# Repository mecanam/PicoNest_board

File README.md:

# PicoNest
ラズパイピコ用の拡張基板です。  
NestBlocksを使用してMicroPythonプログラミングを行います。

## NestBlocks
Scratchのようにブロックでマイコンプログラミング可能な総合開発環境です。  
ブロックは内部でMicroPythonに変換され、マイコンに書き込まれます。
https://nestblocks.jp

# 仕様
- 電源電圧 : 6.5~12V
- サーボ : 4個
- DCモータ : 4個
- ADC : 3個
- GPIO : 5個
- I2C : 2個
- UART : 1個

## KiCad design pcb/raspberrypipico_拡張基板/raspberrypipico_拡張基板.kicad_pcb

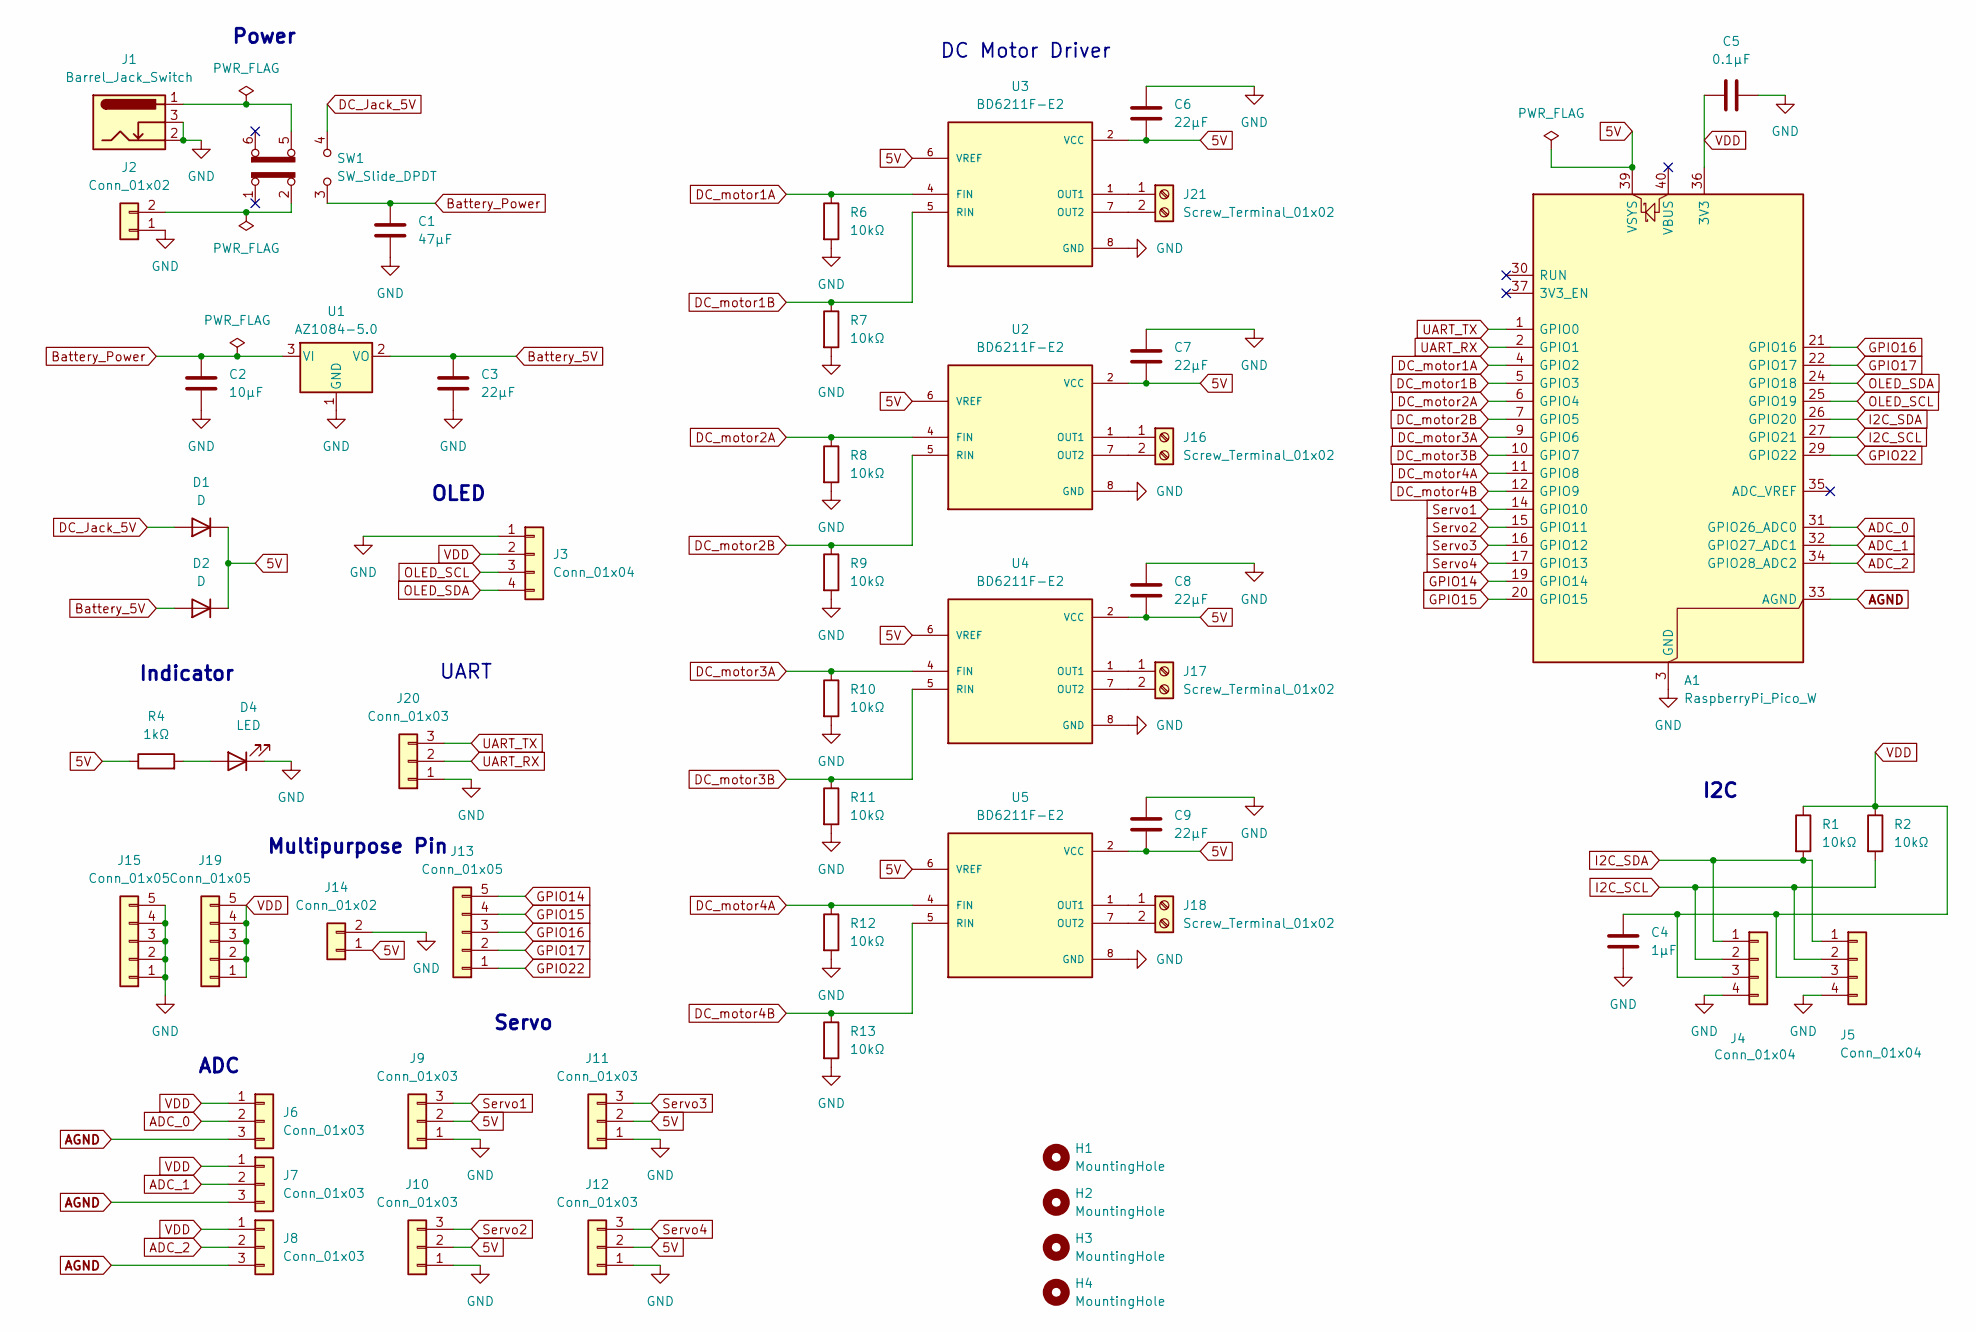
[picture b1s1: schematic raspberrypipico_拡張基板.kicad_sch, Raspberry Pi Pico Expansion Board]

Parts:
A1: RaspberryPi_Pico_W; RaspberryPi_Pico_Common_THT
C1: 47μF; C_Elec_6.3x7.7
C2: 10μF; C_0603_1608Metric_Pad1.08x0.95mm_HandSolder
C3: 22μF; C_0603_1608Metric_Pad1.08x0.95mm_HandSolder
C4: 1μF; C_0603_1608Metric_Pad1.08x0.95mm_HandSolder
C5: 0.1μF; C_0603_1608Metric_Pad1.08x0.95mm_HandSolder
C6, C7, C8, C9: 22μF; C_Elec_6.3x7.7
D1, D2: D; D_SMB_Handsoldering
D4: LED; LED_0603_1608Metric_Pad1.05x0.95mm_HandSolder
H1, H2, H3, H4: MountingHole; MountingHole_3.2mm_M3
J1: Barrel_Jack_Switch; BarrelJack_Horizontal
J2: Conn_01x02; JST_XH_S2B-XH-A_1x02_P2.50mm_Horizontal
J3: Conn_01x04; PinHeader_1x04_P2.54mm_Vertical
J4, J5: Conn_01x04; JST_XH_B4B-XH-A_1x04_P2.50mm_Vertical
J6, J7, J8, J9, J10, J11, J12, J20: Conn_01x03; PinHeader_1x03_P2.54mm_Vertical
J13, J15, J19: Conn_01x05; PinHeader_1x05_P2.54mm_Vertical
J14: Conn_01x02; PinHeader_1x02_P2.54mm_Vertical
J16, J17, J18, J21: Screw_Terminal_01x02; TerminalBlock_bornier-2_P5.08mm
R1, R2, R6, R7, R8, R9, R10, R11, R12, R13: 10kΩ; R_0603_1608Metric_Pad0.98x0.95mm_HandSolder
R4: 1kΩ; R_0603_1608Metric_Pad0.98x0.95mm_HandSolder
SW1: SW_Slide_DPDT; SS22F06G5-G
U1: AZ1084-5.0; TO-252-2
U2, U3, U4, U5: BD6211F-E2; SSOP-8_3.95x5.21x3.27mm_P1.27mm; PARTREV 003

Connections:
5V: A1.39 (VSYS), C6.2, C7.2, C8.2, C9.2, D1.1 (K), D2.1 (K), J9.2, J10.2, J11.2, J12.2, J14.1, R4.1, U2.2 (VCC), U2.3 (VCC), U2.6 (VREF), U3.2 (VCC), U3.3 (VCC), U3.6 (VREF), U4.2 (VCC), U4.3 (VCC), U4.6 (VREF), U5.2 (VCC), U5.3 (VCC), U5.6 (VREF)
ADC_0: A1.31 (GPIO26_ADC0), J6.2
ADC_1: A1.32 (GPIO27_ADC1), J7.2
ADC_2: A1.34 (GPIO28_ADC2), J8.2
AGND: A1.33 (AGND), J6.3, J7.3, J8.3
Battery_5V: C3.1, D2.2 (A), U1.2 (VO)
Battery_Power: C1.1, C2.1, SW1.3 (C), U1.3 (VI)
DC_Jack_5V: D1.2 (A), SW1.4 (A)
DC_motor1A: A1.4 (GPIO2), R6.1, U3.4 (FIN)
DC_motor1B: A1.5 (GPIO3), R7.1, U3.5 (RIN)
DC_motor2A: A1.6 (GPIO4), R8.1, U2.4 (FIN)
DC_motor2B: A1.7 (GPIO5), R9.1, U2.5 (RIN)
DC_motor3A: A1.9 (GPIO6), R10.1, U4.4 (FIN)
DC_motor3B: A1.10 (GPIO7), R11.1, U4.5 (RIN)
DC_motor4A: A1.11 (GPIO8), R12.1, U5.4 (FIN)
DC_motor4B: A1.12 (GPIO9), R13.1, U5.5 (RIN)
GND: A1.3 (GND), A1.8 (GND), A1.13 (GND), A1.18 (GND), A1.23 (GND), A1.28 (GND), A1.38 (GND), C1.2, C2.2, C3.2, C4.2, C5.1, C6.1, C7.1, C8.1, C9.1, D4.1 (K), J1.2, J1.3, J2.1, J3.1, J4.4, J5.4, J9.1, J10.1, J11.1, J12.1, J14.2, J15.1, J15.2, J15.3, J15.4, J15.5, J20.1, R6.2, R7.2, R8.2, R9.2, R10.2, R11.2, R12.2, R13.2, U1.1 (GND), U2.8 (GND), U3.8 (GND), U4.8 (GND), U5.8 (GND)
GPIO14: A1.19 (GPIO14), J13.5
GPIO15: A1.20 (GPIO15), J13.4
GPIO16: A1.21 (GPIO16), J13.3
GPIO17: A1.22 (GPIO17), J13.2
GPIO22: A1.29 (GPIO22), J13.1
I2C_SCL: A1.27 (GPIO21), J4.2, J5.2, R2.2
I2C_SDA: A1.26 (GPIO20), J4.1, J5.1, R1.2
unnamed: D4.2 (A), R4.2
unnamed: J1.1, SW1.5 (B)
unnamed: J2.2, SW1.2 (B)
unnamed: J16.1, U2.1 (OUT1)
unnamed: J16.2, U2.7 (OUT2)
unnamed: J17.1, U4.1 (OUT1)
unnamed: J17.2, U4.7 (OUT2)
unnamed: J18.1, U5.1 (OUT1)
unnamed: J18.2, U5.7 (OUT2)
unnamed: J21.1, U3.1 (OUT1)
unnamed: J21.2, U3.7 (OUT2)
OLED_SCL: A1.25 (GPIO19), J3.3
OLED_SDA: A1.24 (GPIO18), J3.4
Servo1: A1.14 (GPIO10), J9.3
Servo2: A1.15 (GPIO11), J10.3
Servo3: A1.16 (GPIO12), J11.3
Servo4: A1.17 (GPIO13), J12.3
UART_RX: A1.2 (GPIO1), J20.2
UART_TX: A1.1 (GPIO0), J20.3
VDD: A1.36 (3V3), C4.1, C5.2, J3.2, J4.3, J5.3, J6.1, J7.1, J8.1, J19.1, J19.2, J19.3, J19.4, J19.5, R1.1, R2.1

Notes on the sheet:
I2C
Indicator
Power
Servo
ADC
DC Motor Driver
UART
OLED
Multipurpose Pin

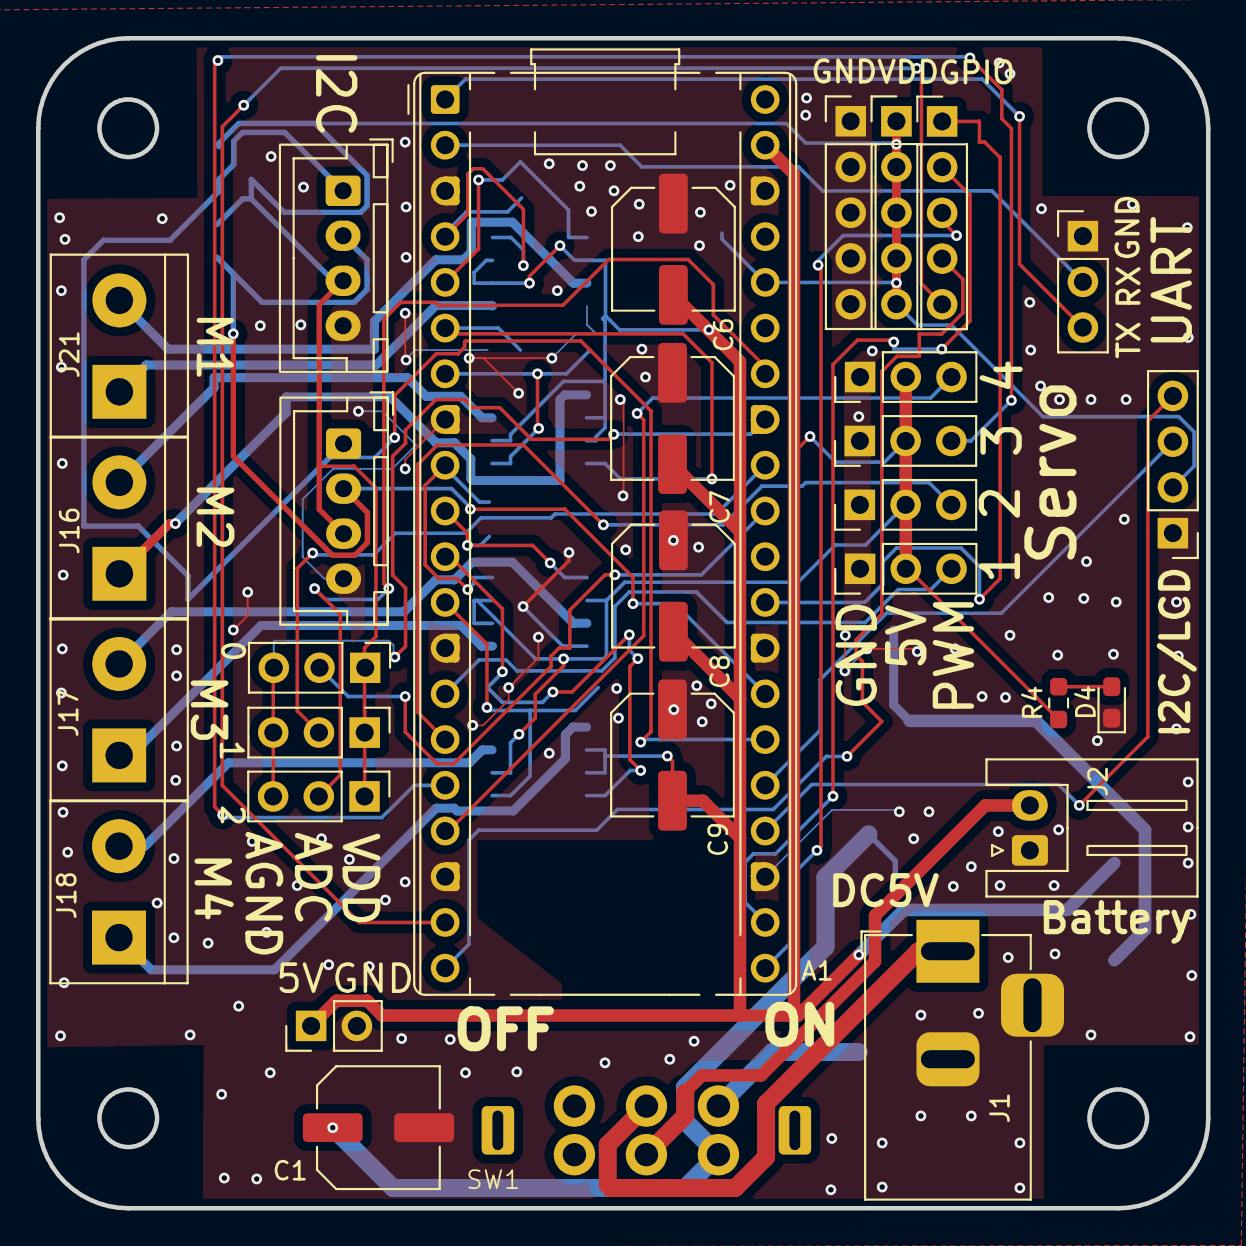
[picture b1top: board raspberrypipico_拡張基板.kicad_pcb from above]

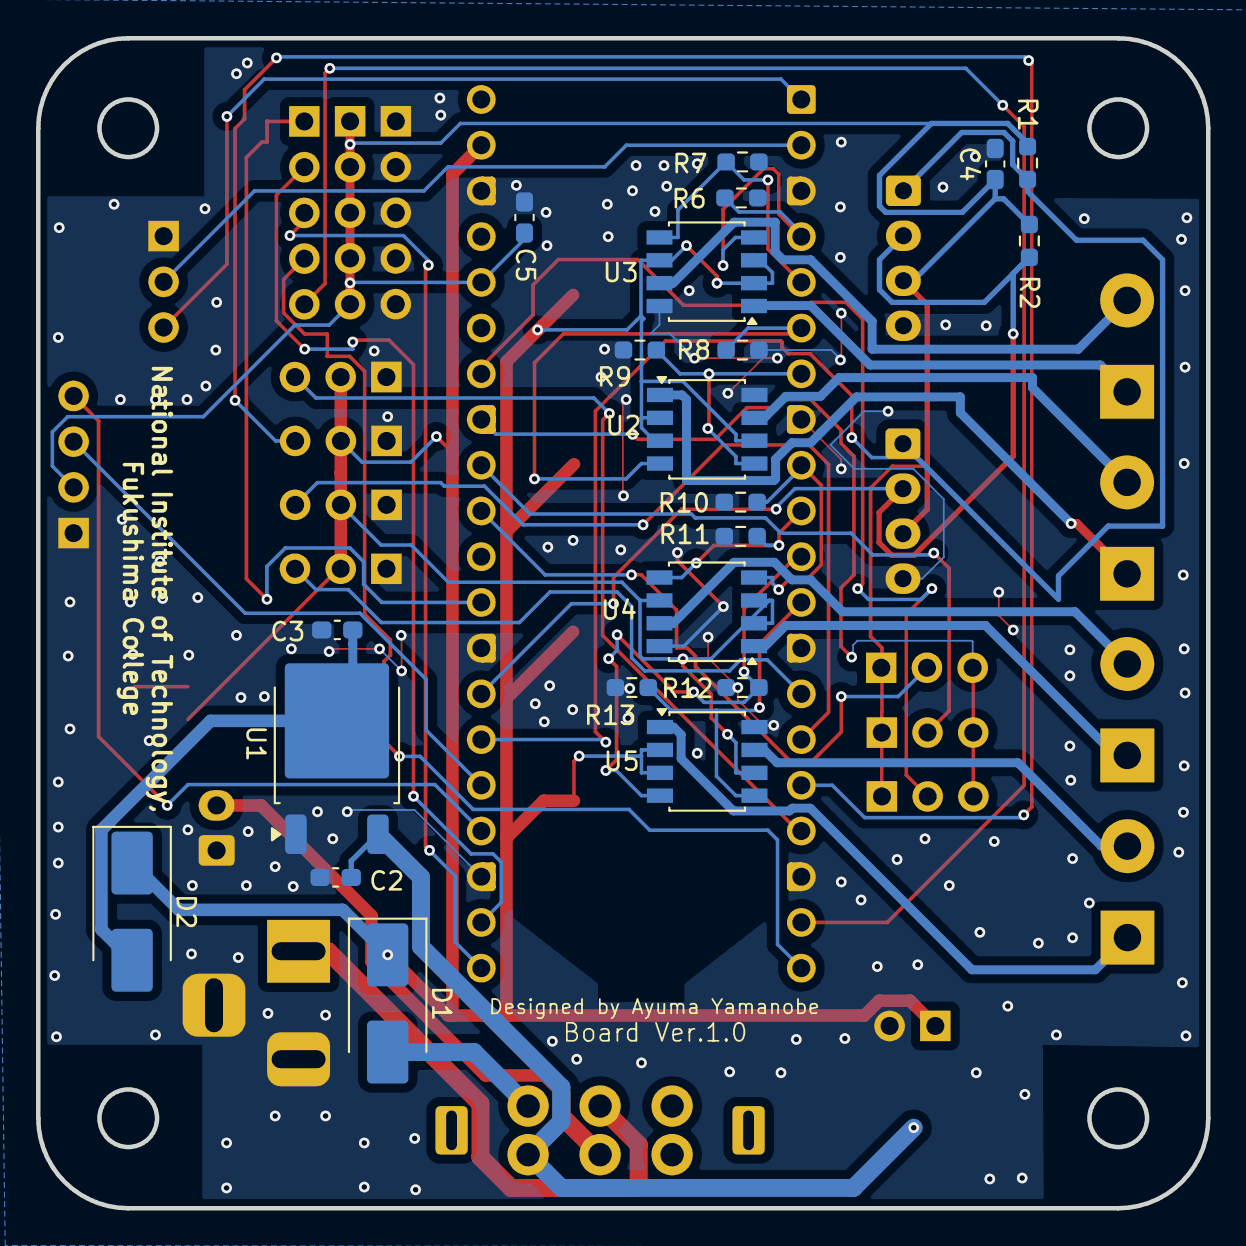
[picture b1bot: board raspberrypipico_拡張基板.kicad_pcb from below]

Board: 2 copper layers, 65.0 x 65.0 mm, 55 parts (21 on the bottom side), 44 nets.
